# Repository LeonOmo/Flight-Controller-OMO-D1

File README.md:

# Flight-Controller-FC-D1

A custom designed, minimalistic STM32F722RET6 based flight controller built from scratch for custom drone and aerospace experimentation.

## What is this project?

Flight Controller D1: is a custom made circuit board designed specifically to act as an stabilization unit for stabilising platforms. It breaks away from bulky flight controllers by packing only the essential, minimal form factor powered by an STM32 microcontroller and a modern BMI270.

## Purpose & What it does

The primary purpose of this board is to process orientation data. 
- Attitude: Reads high speed gyro and accelerometer data via the BMI270 sensor to keep the aircraft stable.
- Motor Control: Provides 4 dedicated motor output attachments to drive electronic speed controllers (ESCs) or micro motors.

## Why does it exist?

Building an off the shelf drone is fun, but designing the core avionics from the ground up teaches you how hardware, firmware, and circuit layout actually interact in the real world. 

- Aerospace Passion: As a personal stepping stone for aerospace and rocketry drone payloads having total control over a custom flight controller design opens up endless possibilities for tailored form factors.
- Just for Fun: Pure engineering curiosity testing whether a self routed PCB built in KiCAD can successfully boot, communicate, and stabilize a flight platform. (As of now, it's a first prototype fingers crossed that everything works as intended!)

## BOM

| Designator | Component | LCSC Part Number / Link | Description |
| :--- | :--- | :--- | :--- |
| U1 | STM32F722RET6 | C118207 | Main MCU |
| U4 | BMI270 | C2836813 | Gyro and accelerometer |
| U2 | AMS1117-3.3 | C5632159 | 3.3V regulator |
| X1 | X322525MOB4SI | C9006 | 25MHz crystal |
| X2 | Q13FC1350000400 | C32346 | 32.768kHz crystal |
| L1 | FCM1608KF-601T03 | C141723 | Ferrite bead |
| D1, D2 | XL-1608SURC-06 | C965799 | Status LEDs |
| D3, D4 | Schottky diode | C7370889 | Input diodes |
| SW1, SW2 | TS-1088-AR02016 | C720477 | BOOT and RESET buttons |
| C1, C2, C3 | 100nF | C1525 | Decoupling capacitors |
| C4, C7, C8, C9 | 20pF | C1554 | Crystal load capacitors |
| C5 | 22µF | C59461 | Regulator output capacitor |
| C6 | 10µF | C19702 | Regulator input capacitor |
| C10 | 2.2µF | C386031 | VCAP capacitor |
| C11, C12, C13 | 1µF | C52923 | Decoupling capacitors |
| C14 | 10µF | C15525 | Bulk capacitor |
| C15, C16, C17, C18, C19 | 100nF | C5142565 | Decoupling capacitors |
| R1 | 10k | C54530535 | BOOT0 pull-down |
| R4, R5 | 5.1k | C23186 | USB-C resistors |
| R2, R3 | 470 | C23179 | LED resistors |
| J1 | USB_C_Receptacle_USB2.0_16P | C9900184415 | USB C Connector |
| PCB | | | https://jlcpcb.com/ |

## Tools & Technologies

- PCB Design: KiCAD
- Firmware: None yet but with STm32cube

## Schematics & PCB Layout

## Schematic

## PCB

## Extras

I liked this way more than id like to admit making this was really fun for me and it was just so freeing.

## Bonus

Before settling on the BMI270, early iterations used the older MPU6050. Transitioning away from it was a major hurdle due to its age and lack of modern integration support, making the shift to the BMI270 a much cleaner and more reliable choice for modern layouts.

Also an old version of the FC.

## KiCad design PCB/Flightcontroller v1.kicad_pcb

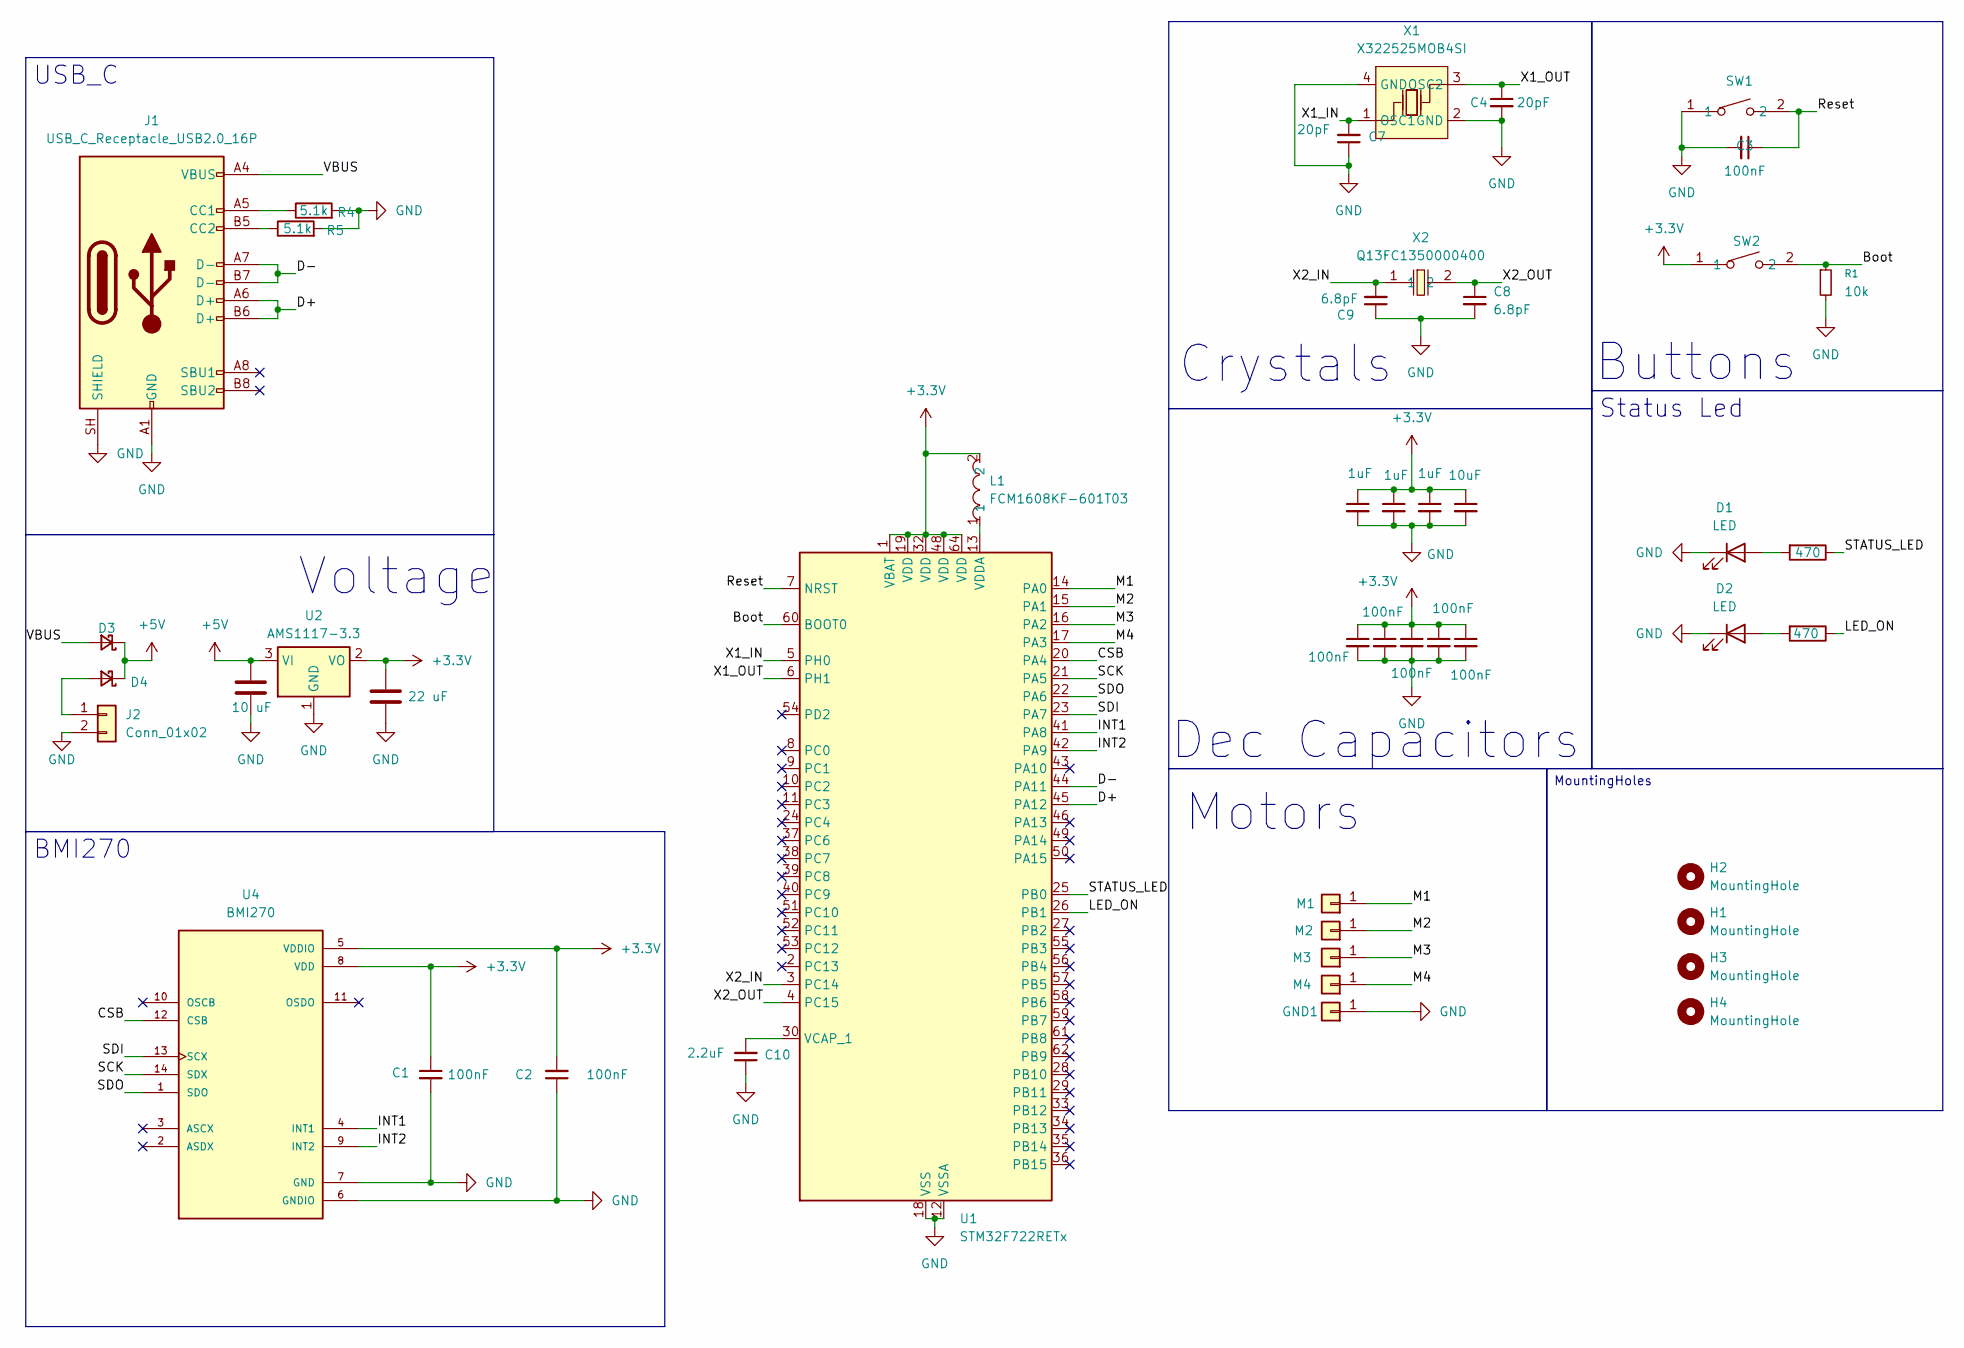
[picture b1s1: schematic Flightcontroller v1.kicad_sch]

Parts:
C1, C2, C3: 100nF; C_0402_1005Metric
C4, C7: 20pF; C_0402_1005Metric
C5: 22 uF; C_0603_1608Metric
C6: 10 uF; C_0603_1608Metric
C8, C9: 6.8pF; C_0402_1005Metric
C10: 2.2uF; C_0201_0603Metric
C11, C12, C13: 1uF; C_0402_1005Metric
C14: 10uF; C_0402_1005Metric
C15, C16, C17, C18, C19: 100nF; C_0201_0603Metric
D1, D2: LED; LED_0603_1608Metric
D3, D4: D_Schottky_Small; D_SOD-123
GND1: Conn_01x01; TestPoint_Pad_D1.5mm
H1, H2, H3, H4: MountingHole; MountingHole_3.2mm_M3
J1: USB_C_Receptacle_USB2.0_16P; USB_C_Receptacle_GCT_USB4105-xx-A_16P_TopMnt_Horizontal
J2: Conn_01x02; SolderWire-0.5sqmm_1x02_P4.6mm_D0.9mm_OD2.1mm
L1: FCM1608KF-601T03; L0603; MPN FCM1608KF-601T03; LCSC Part C141723
M1, M2, M3, M4: Conn_01x01; TestPoint_Pad_D1.5mm
R1: 10k; R_0201_0603Metric
R4, R5: 5.1k; R_0603_1608Metric
R8, R460: 470; R_0603_1608Metric
SW1, SW2: TS-1088-AR02016; SW-SMD_L3.9-W3.0-P4.45; MPN TS-1088-AR02016; LCSC Part C720477
U1: STM32F722RETx; LQFP-64_10x10mm_P0.5mm
U2: AMS1117-3.3; TO-252-2
U4: BMI270; XDCR_BMI270
X1: X322525MOB4SI; CRYSTAL-SMD_4P-L3.2-W2.5-BL; MPN X322525MOB4SI; LCSC Part C9006
X2: Q13FC1350000400; FC-135R_L3.2-W1.5; MPN Q13FC13500004; LCSC Part C32346

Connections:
+3.3V: C1.1, C2.2, C5.1, C11.1, C12.1, C13.1, C14.1, C15.1, C16.1, C17.1, C18.1, C19.1, L1.2, SW2.1, U1.1 (VBAT), U1.19 (VDD), U1.32 (VDD), U1.48 (VDD), U1.64 (VDD), U2.2 (VO), U4.5 (VDDIO), U4.8 (VDD); also elsewhere on the board
+5V: C6.1, D3.1 (K), D4.1 (K), U2.3 (VI)
/Boot: R1.1, SW2.2, U1.60 (BOOT0); also elsewhere on the board
/CSB: U1.20 (PA4), U4.12 (CSB)
/D+: J1.A6 (D+), J1.B6 (D+), U1.45 (PA12)
/D-: J1.A7 (D-), J1.B7 (D-), U1.44 (PA11)
/INT1: U1.41 (PA8), U4.4 (INT1)
/INT2: U1.42 (PA9), U4.9 (INT2)
/LED_ON: R460.1, U1.26 (PB1)
/M1: M1.1 (Pin_1_1), U1.14 (PA0)
/M2: M2.1 (Pin_1_1), U1.15 (PA1)
/M3: M3.1 (Pin_1_1), U1.16 (PA2)
/M4: M4.1 (Pin_1_1), U1.17 (PA3)
/Reset: C3.1, SW1.2, U1.7 (NRST); also elsewhere on the board
/SCK: U1.21 (PA5), U4.14 (SDX)
/SDI: U1.23 (PA7), U4.13 (SCX)
/SDO: U1.22 (PA6), U4.1 (SDO)
/STATUS_LED: R8.1, U1.25 (PB0)
/VBUS: D3.2 (A), J1.A4 (VBUS), J1.A9 (VBUS), J1.B4 (VBUS), J1.B9 (VBUS)
/X1_IN: C7.2, U1.5 (PH0), X1.1 (OSC1)
/X1_OUT: C4.1, U1.6 (PH1), X1.3 (OSC2)
/X2_IN: C9.2, U1.3 (PC14), X2.1
/X2_OUT: C8.1, U1.4 (PC15), X2.2
GND: C1.2, C2.1, C3.2, C4.2, C5.2, C6.2, C7.1, C8.2, C9.1, C10.1, C11.2, C12.2, C13.2, C14.2, C15.2, C16.2, C17.2, C18.2, C19.2, D1.1 (K), D2.1 (K), GND1.1 (Pin_1_1), J1.A1 (GND), J1.A12 (GND), J1.B1 (GND), J1.B12 (GND), J1.SH (SHIELD), J2.2, R1.2, R4.2, R5.2, SW1.1, U1.12 (VSSA), U1.18 (VSS), U1.31 (VSS), U1.47 (VSS), U1.63 (VSS), U2.1 (GND), U4.6 (GNDIO), U4.7 (GND), X1.2 (GND), X1.4 (GND); also elsewhere on the board
unnamed: D1.2 (A), R8.2
unnamed: D2.2 (A), R460.2
unnamed: D4.2 (A), J2.1
unnamed: J1.A5 (CC1), R4.1
unnamed: J1.B5 (CC2), R5.1
unnamed: C10.2, U1.30 (VCAP_1)
unnamed: L1.1, U1.13 (VDDA)

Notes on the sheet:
Crystals
Motors
Buttons
Dec Capacitors
Voltage
MountingHoles
USB_C
Status Led
BMI270

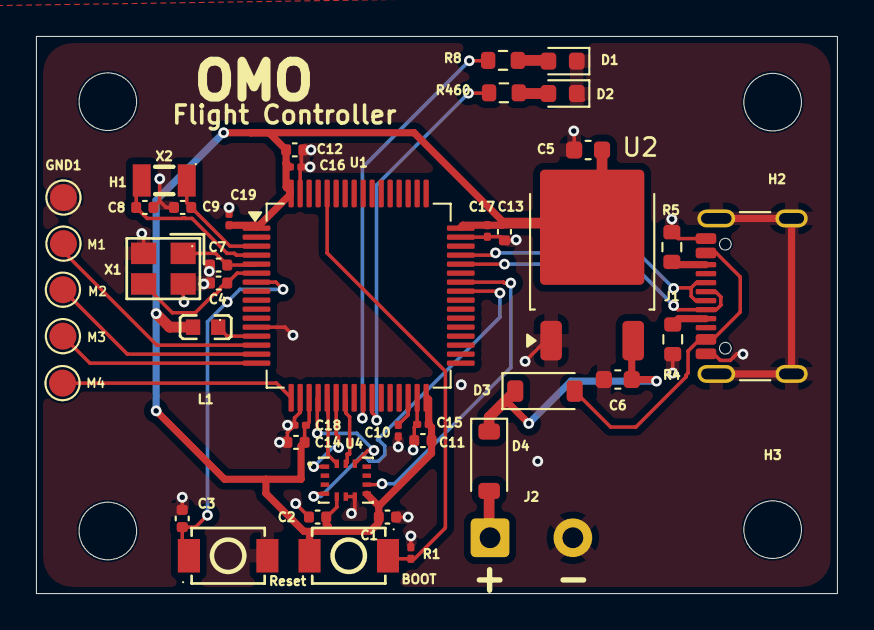
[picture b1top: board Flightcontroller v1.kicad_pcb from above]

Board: 2 copper layers, 44.5 x 31.0 mm, 47 parts (0 on the bottom side), 31 nets.

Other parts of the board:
BOOT: TS-1088-AR02016; SW-SMD_L3.9-W3.0-P4.45
Reset: TS-1088-AR02016; SW-SMD_L3.9-W3.0-P4.45

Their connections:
+3.3V: BOOT.1; also elsewhere on the board
/Boot: BOOT.2; also elsewhere on the board
/Reset: Reset.2; also elsewhere on the board
GND: Reset.1; also elsewhere on the board

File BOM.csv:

| Designator | Component | LCSC Part Number / Link | Description |
| :--- | :--- | :--- | :--- |
| U1 | STM32F722RET6 | C118207 | Main MCU |
| U4 | BMI270 | C2836813 | Gyro and accelerometer |
| U2 | AMS1117-3.3 | C5632159 | 3.3V regulator |
| X1 | X322525MOB4SI | C9006 | 25MHz crystal |
| X2 | Q13FC1350000400 | C32346 | 32.768kHz crystal |
| L1 | FCM1608KF-601T03 | C141723 | Ferrite bead |
| D1, D2 | XL-1608SURC-06 | C965799 | Status LEDs |
| D3, D4 | Schottky diode | C7370889 | Input diodes |
| SW1, SW2 | TS-1088-AR02016 | C720477 | BOOT and RESET buttons |
| C1, C2, C3 | 100nF | C1525 | Decoupling capacitors |
| C4, C7, C8, C9 | 20pF | C1554 | Crystal load capacitors |
| C5 | 22µF | C59461 | Regulator output capacitor |
| C6 | 10µF | C19702 | Regulator input capacitor |
| C10 | 2.2µF | C386031 | VCAP capacitor |
| C11, C12, C13 | 1µF | C52923 | Decoupling capacitors |
| C14 | 10µF | C15525 | Bulk capacitor |
| C15, C16, C17, C18, C19 | 100nF | C5142565 | Decoupling capacitors |
| R1 | 10k | C54530535 | BOOT0 pull-down |
| R4, R5 | 5.1k | C23186 | USB-C resistors |
| R2, R3 | 470 | C23179 | LED resistors |
| J1 | USB_C_Receptacle_USB2.0_16P | C9900184415 | USB C Connector |
| PCB | | | https://jlcpcb.com/ |
| Total ||||
